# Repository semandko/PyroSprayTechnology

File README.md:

# PyroSprayTechnology
Pyro spray technology for deposition of organic solution of semiconductor compositions

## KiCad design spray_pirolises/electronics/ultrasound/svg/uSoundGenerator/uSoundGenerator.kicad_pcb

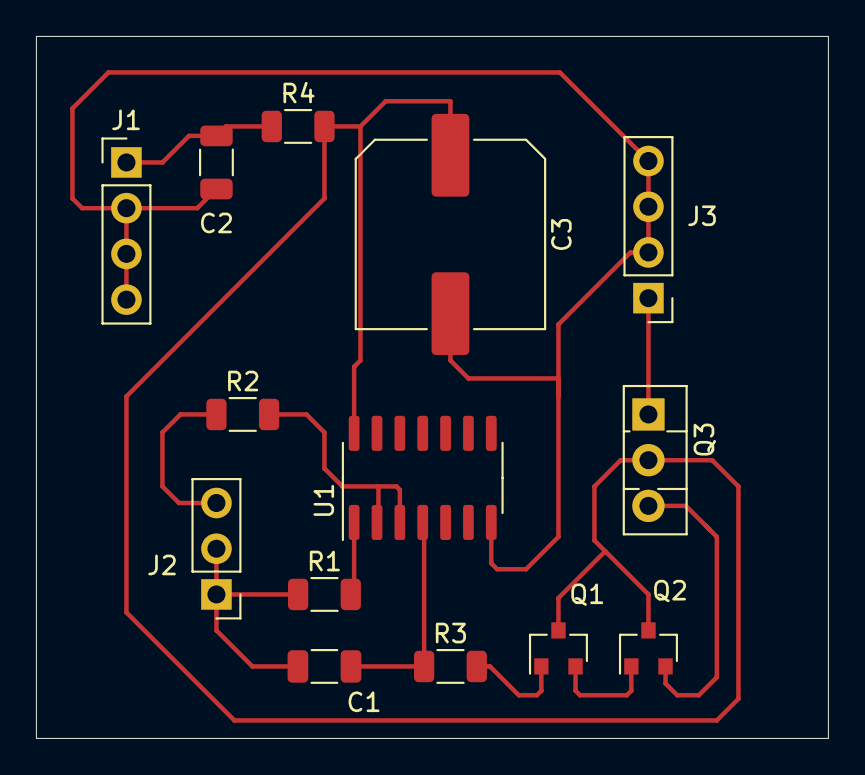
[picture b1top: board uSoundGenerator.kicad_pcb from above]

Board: 2 copper layers, 44.0 x 39.0 mm, 14 parts (0 on the bottom side), 12 nets.

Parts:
C1: 1n; C_1206_3216Metric
C2: 100n; C_1206_3216Metric
C3: 1000mk; C_Elec_10x10.2
J1, J3: Conn_01x04_Female; PinHeader_1x04_P2.54mm_Vertical
J2: Conn_01x03_Male; PinHeader_1x03_P2.54mm_Vertical
Q1, Q2: BC846; SOT-23
Q3: BD237; TO-126-3_Vertical
R1: 100k; R_1206_3216Metric
R2: 0K1; R_1206_3216Metric
R3: 2k; R_1206_3216Metric
R4: 3k; R_1206_3216Metric
U1: 4069; SOIC-14_3.9x8.7mm_P1.27mm

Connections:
+12V: C2.1, J1.1, R4.1
GND: C2.2, C3.2, J1.2, J1.3, J1.4, J3.2, J3.3, J3.4, U1.7
unnamed: C1.1, J2.1, J2.2, R1.1
unnamed: C1.2, R3.1, U1.4
unnamed: C3.1, Q1.3, Q2.3, Q3.2, R4.2, U1.14
unnamed: J2.3, R2.1
unnamed: J3.1, Q3.1
unnamed: Q1.1, R3.2
unnamed: Q1.2, Q2.1
unnamed: Q2.2, Q3.3
unnamed: R1.2, U1.1
unnamed: R2.2, U1.2, U1.3

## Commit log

2023-09-17 change ignore
2023-09-17 init
2023-09-17 electronics
2023-09-19 add zineb materials
